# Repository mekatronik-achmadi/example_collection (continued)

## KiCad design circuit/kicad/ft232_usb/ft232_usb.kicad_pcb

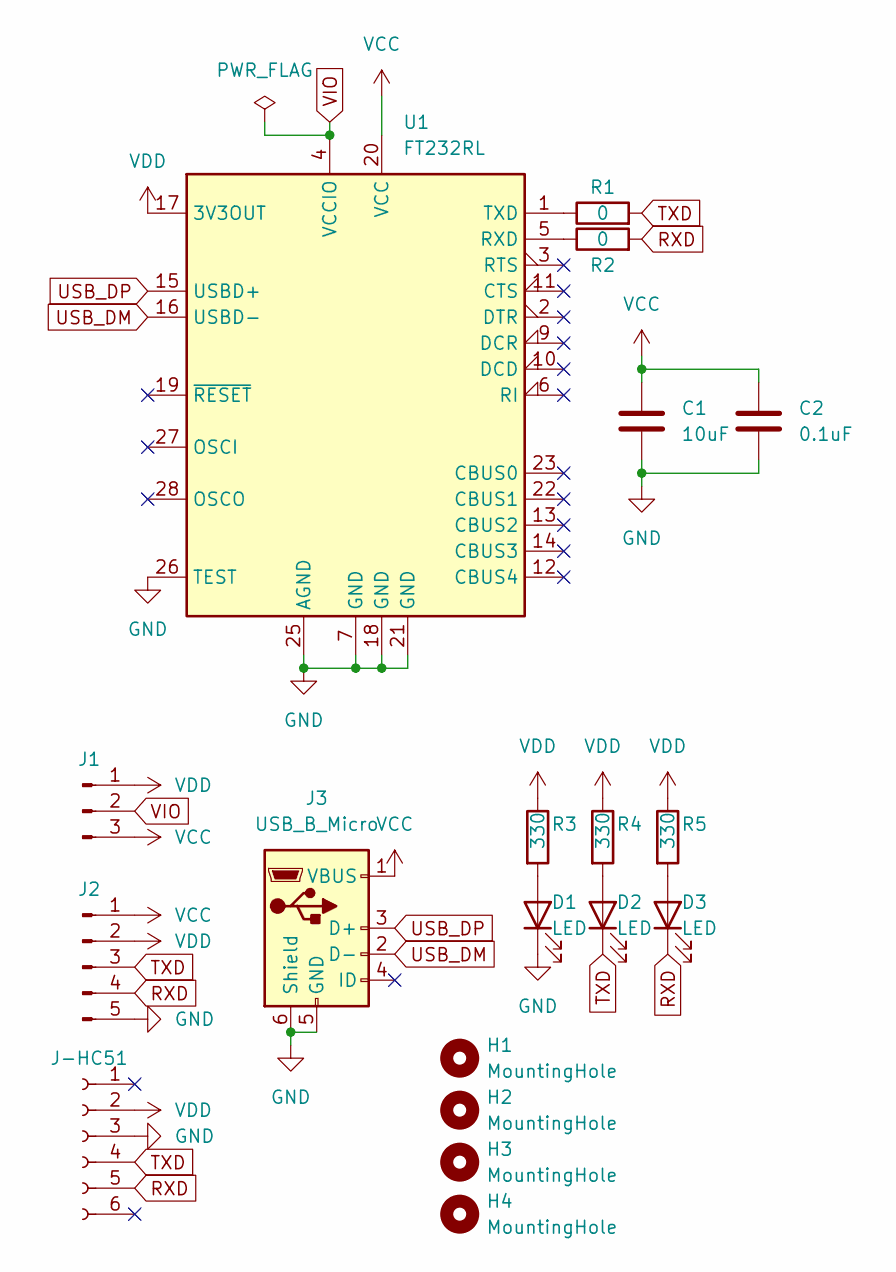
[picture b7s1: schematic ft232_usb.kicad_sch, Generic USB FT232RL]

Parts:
C1: 10uF; C_0805_2012Metric_Pad1.18x1.45mm_HandSolder
C2: 0.1uF; C_0805_2012Metric_Pad1.18x1.45mm_HandSolder
D1, D2, D3: LED; LED_0805_2012Metric_Pad1.15x1.40mm_HandSolder
H1, H2, H3, H4: MountingHole; MountingHole_2.2mm_M2_ISO7380_Pad
J1: Conn_01x03_Male; PinHeader_1x03_P2.54mm_Vertical
J2: Conn_01x05_Male; PinHeader_1x05_P2.54mm_Vertical
J3: USB_B_Micro; USB_Micro-B_Wuerth_629105150521
J-HC51: Conn_01x06_Female; PinSocket_1x06_P2.54mm_Vertical
R1, R2: 0; R_0805_2012Metric_Pad1.20x1.40mm_HandSolder
R3, R4, R5: 330; R_0805_2012Metric_Pad1.20x1.40mm_HandSolder
U1: FT232RL; SSOP-28_5.3x10.2mm_P0.65mm

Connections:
GND: C1.2, C2.2, D1.1 (K), J2.5, J3.5 (GND), J3.6 (Shield), J-HC51.3, U1.7 (GND), U1.18 (GND), U1.21 (GND), U1.25 (AGND), U1.26 (TEST)
unnamed: D1.2 (A), R3.2
unnamed: D2.2 (A), R4.2
unnamed: D3.2 (A), R5.2
unnamed: R1.1, U1.1 (TXD)
unnamed: R2.1, U1.5 (RXD)
RXD: D3.1 (K), J2.4, J-HC51.5, R2.2
TXD: D2.1 (K), J2.3, J-HC51.4, R1.2
USB_DM: J3.2 (D-), U1.16 (USBD-)
USB_DP: J3.3 (D+), U1.15 (USBD+)
VCC: C1.1, C2.1, J1.3, J2.1, J3.1 (VBUS), U1.20 (VCC)
VDD: J1.1, J2.2, J-HC51.2, R3.1, R4.1, R5.1, U1.17 (3V3OUT)
VIO: J1.2, U1.4 (VCCIO)

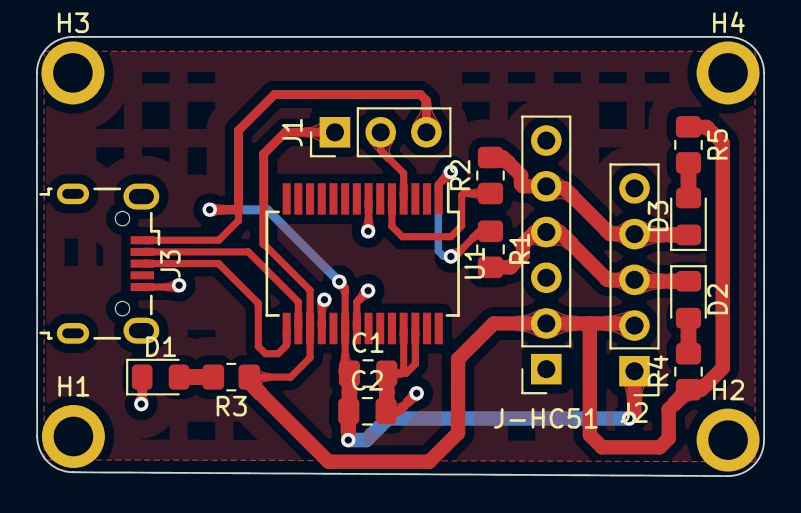
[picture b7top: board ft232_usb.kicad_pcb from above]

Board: 2 copper layers, 40.4 x 24.4 mm, 19 parts (0 on the bottom side), 13 nets.

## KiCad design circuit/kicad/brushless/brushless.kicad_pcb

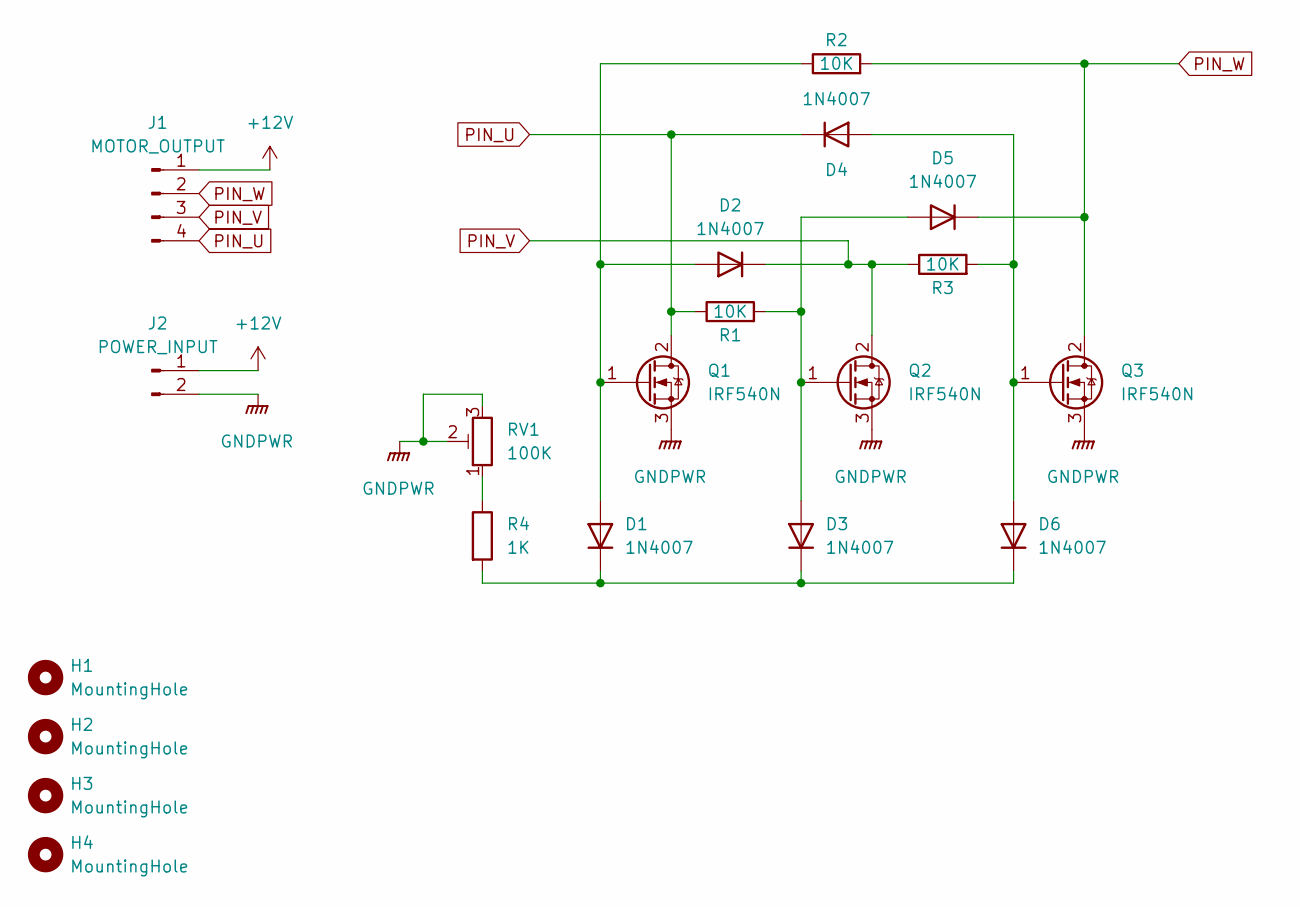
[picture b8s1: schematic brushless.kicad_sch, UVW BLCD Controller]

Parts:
D1, D2, D3, D4, D5, D6: 1N4007; D_SMA-SMB_Universal_Handsoldering
H1, H2, H3, H4: MountingHole; MountingHole_2.5mm
J1: MOTOR_OUTPUT; Altech_AK300_1x04_P5.00mm_45-Degree
J2: POWER_INPUT; Altech_AK300_1x02_P5.00mm_45-Degree
Q1, Q2, Q3: IRF540N; TO-263-2
R1, R2, R3: 10K; R_1206_3216Metric_Pad1.30x1.75mm_HandSolder
R4: 1K; R_1206_3216Metric_Pad1.30x1.75mm_HandSolder
RV1: 100K; Potentiometer_Bourns_3266W_Vertical

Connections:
+12V: J1.1, J2.1
GNDPWR: J2.2, Q1.3 (S), Q2.3 (S), Q3.3 (S), RV1.2, RV1.3
unnamed: D1.2 (A), D2.2 (A), Q1.1 (G), R2.1
unnamed: D3.2 (A), D5.2 (A), Q2.1 (G), R1.2
unnamed: D4.2 (A), D6.2 (A), Q3.1 (G), R3.2
unnamed: D1.1 (K), D3.1 (K), D6.1 (K), R4.2
unnamed: R4.1, RV1.1
PIN_U: D4.1 (K), J1.4, Q1.2 (D), R1.1
PIN_V: D2.1 (K), J1.3, Q2.2 (D), R3.1
PIN_W: D5.1 (K), J1.2, Q3.2 (D), R2.2

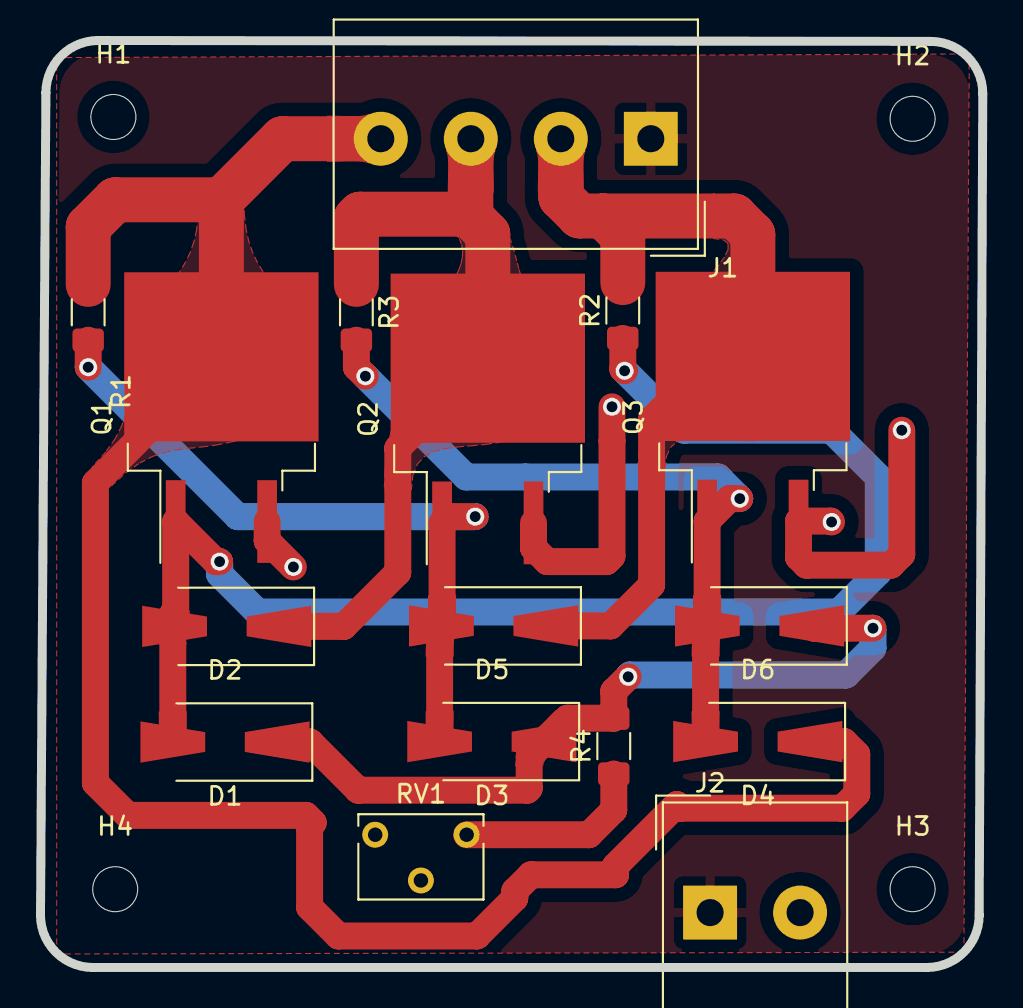
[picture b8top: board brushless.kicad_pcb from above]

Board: 2 copper layers, 52.3 x 51.5 mm, 20 parts (0 on the bottom side), 10 nets.

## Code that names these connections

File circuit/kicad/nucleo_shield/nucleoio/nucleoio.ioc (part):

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Mcu.Name=STM32F401R(D-E)Tx
Mcu.Package=LQFP64
Mcu.UserName=STM32F401RETx
PA10.Mode=Asynchronous
PA10.Signal=USART1_RX
PA13.GPIOParameters=GPIO_Label
PA13.GPIO_Label=TMS
PA13.Mode=Serial_Wire
PA13.Signal=SYS_JTMS-SWDIO
PA14.GPIOParameters=GPIO_Label
PA14.GPIO_Label=TCK
PA14.Mode=Serial_Wire
PA14.Signal=SYS_JTCK-SWCLK
PA15.Mode=NSS_Signal_Hard_Output
PA15.Signal=SPI3_NSS
PA2.GPIOParameters=GPIO_Speed,GPIO_PuPd,GPIO_Label,GPIO_Mode
PA2.GPIO_Label=USART_TX
PA2.GPIO_Mode=GPIO_MODE_AF_PP
PA2.GPIO_PuPd=GPIO_NOPULL
PA2.GPIO_Speed=GPIO_SPEED_FREQ_LOW
PA2.Mode=Asynchronous
PA2.Signal=USART2_TX
PA3.GPIOParameters=GPIO_Speed,GPIO_PuPd,GPIO_Label,GPIO_Mode
PA3.GPIO_Label=USART_RX
PA3.GPIO_Mode=GPIO_MODE_AF_PP
PA3.GPIO_PuPd=GPIO_NOPULL
PA3.GPIO_Speed=GPIO_SPEED_FREQ_LOW
PA3.Mode=Asynchronous
PA3.Signal=USART2_RX
PA5.GPIOParameters=GPIO_Speed,GPIO_PuPd,GPIO_Label,GPIO_Mode
PA5.GPIO_Label=LD2 [Green Led]
PA5.GPIO_Mode=GPIO_MODE_OUTPUT_PP
PA5.GPIO_PuPd=GPIO_NOPULL
PA5.GPIO_Speed=GPIO_SPEED_FREQ_LOW
PA5.Signal=GPIO_Output
PA9.Mode=Asynchronous
PA9.Signal=USART1_TX
PB2.Signal=GPIO_Input
PB3.GPIOParameters=GPIO_Label
PB3.GPIO_Label=SWO
PB3.Signal=SYS_JTDO-SWO
PC10.Mode=Full_Duplex_Master
PC10.Signal=SPI3_SCK
PC11.Mode=Full_Duplex_Master
PC11.Signal=SPI3_MISO
PC12.Mode=Full_Duplex_Master
PC12.Signal=SPI3_MOSI
PC13-ANTI_TAMP.GPIOParameters=GPIO_PuPd,GPIO_Label,GPIO_ModeDefaultEXTI
PC13-ANTI_TAMP.GPIO_Label=B1 [Blue PushButton]
PC13-ANTI_TAMP.GPIO_ModeDefaultEXTI=GPIO_MODE_IT_FALLING
PC13-ANTI_TAMP.GPIO_PuPd=GPIO_NOPULL
PC13-ANTI_TAMP.Signal=GPXTI13
PC14-OSC32_IN.Mode=LSE-External-Oscillator
PC14-OSC32_IN.Signal=RCC_OSC32_IN
PC15-OSC32_OUT.Mode=LSE-External-Oscillator
PC15-OSC32_OUT.Signal=RCC_OSC32_OUT
PH0\ -\ OSC_IN.Mode=HSE-External-Clock-Source
PH0\ -\ OSC_IN.Signal=RCC_OSC_IN
PH1\ -\ OSC_OUT.Mode=HSE-External-Clock-Source
PH1\ -\ OSC_OUT.Signal=RCC_OSC_OUT
RCC.HSE_VALUE=8000000
RCC.SYSCLKFreq_VALUE=84000000
RCC.SYSCLKSource=RCC_SYSCLKSOURCE_PLLCLK
board=NUCLEO-F401RE
boardIOC=true

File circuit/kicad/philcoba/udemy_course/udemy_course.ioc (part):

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Mcu.Name=STM32F103C(8-B)Tx
Mcu.Package=LQFP48
Mcu.UserName=STM32F103C8Tx
PA11.Mode=Device
PA11.Signal=USB_DM
PA12.Mode=Device
PA12.Signal=USB_DP
PA13.Mode=Serial_Wire
PA13.Signal=SYS_JTMS-SWDIO
PA14.Mode=Serial_Wire
PA14.Signal=SYS_JTCK-SWCLK
PB10.Mode=I2C
PB10.Signal=I2C2_SCL
PB11.Mode=I2C
PB11.Signal=I2C2_SDA
PB6.Mode=Asynchronous
PB6.Signal=USART1_TX
PB7.Mode=Asynchronous
PB7.Signal=USART1_RX
PC13-TAMPER-RTC.Signal=GPIO_Output
PD0-OSC_IN.Mode=HSE-External-Oscillator
PD0-OSC_IN.Signal=RCC_OSC_IN
PD1-OSC_OUT.Mode=HSE-External-Oscillator
PD1-OSC_OUT.Signal=RCC_OSC_OUT
RCC.SYSCLKFreq_VALUE=48000000
RCC.SYSCLKSource=RCC_SYSCLKSOURCE_PLLCLK
board=custom

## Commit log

2021-11-26 first Flutter
2021-11-26 first atmega
2021-11-26 more atmega
2021-11-26 first esp8266
2021-11-26 mqtt esp8266
2021-11-26 doorwatch esp8266
2021-11-26 phtdsmeter esp8266
2021-11-26 first rtos esp8266
2021-11-26 esp8266
2021-11-27 first stm32
2021-11-27 stm32
2021-11-27 m2560_las_orbit
2021-11-29 ta nya didin
2021-11-30 stm32 more examples
2021-12-15 f429disc examples
2021-12-15 c webkit
2021-12-15 new circuit
2021-12-15 mega16_training
2021-12-15 wxserial
2021-12-16 more kicad examples
2021-12-16 gtk examples
2021-12-16 java examples
2021-12-16 octave examples
2021-12-16 more examples
2021-12-16 python academic examples
2021-12-16 qt examples
2021-12-16 stm32 chibios examples
2021-12-16 finish selecting examples
2021-12-16 clean-up unnecessary non text files
2021-12-16 some stm32 examples
2021-12-16 esp32 examples
2022-01-05 update stm32 sensor example
2022-01-11 Mini PV
2022-01-11 PCB Mini PV
2022-01-16 esp32 blink
2022-01-16 esp8266 example
2022-02-18 papank PCB
2022-02-18 esp32 dsp example
2022-02-18 ESP DSP FFT is weird
2022-02-19 esp32 mic fft doxygen
2022-02-19 esp32 mic fft doxygen dark
2022-02-20 doxygen
2022-02-25 KiCAD tutorial
2022-02-26 SMD Tutorial
2022-03-04 wxWidget CPP
2022-03-14 btserial
2022-03-14 btserial_keypad
2022-03-14 btspp
2022-03-14 btspp OLED
2022-03-14 btspp string handle
2022-03-14 bt spp text handler
2022-03-15 string/char handler error
2022-03-15 need handle sring more than 20
2022-03-15 string handle
2022-03-15 40 strings OK
2022-03-15 first demo
2022-03-15 Include PDF schematic
2022-03-24 coba js server
2022-04-09 stm32 driver
2022-05-21 pid example in python
2022-07-20 ESP32 IDF Arduino Example
2022-07-20 ESP OLED IDF
2022-07-20 ESP IDF
2022-07-20 ESP32 OLED IDF
2022-07-20 ESP32 IDF OLED
2022-07-20 ESP32 OLED Arduino
2022-07-20 ESP32 Arduino
2022-07-20 Typo
2022-07-20 Arduino sucks
2022-07-21 ESP32 Arduino compileable but LCD blank
2022-07-21 ESP32 Arduino OLED Example
2022-07-21 ESP32 Arduino OLED done
2022-09-08 ESP32 Audio Tester
2022-09-08 Schematic Done
2022-09-08 ESP32 Audio
2022-09-20 some examples
2022-10-02 ESP32 AP Webserver
2022-10-02 ESP32 Version
2022-10-02 ESP32 HTTPD
2022-12-27 KiCAD JLC Tutorial
2022-12-27 KiCAD JLC
2022-12-31 Serial Example
2022-12-31 WX serial
2022-12-31 Cross Serial Terminal wxWidget
2022-12-31 Cross Serial Terminal Qt
2022-12-31 Cross Serial Qt
2023-01-01 Cross Serial Gtk
2023-01-02 GTK is so weird
2023-01-02 GTK GUI Serial
2023-01-02 GTK is weird
2023-01-02 Readme Cross Serial
2023-01-03 Gtk has no input dialog like Qt or wxWidgets
2023-01-03 Port/Baudrate no Input Dialog
2023-01-03 Cross Serial Qt Update
2023-01-03 Some basic AVR example
2023-01-03 AVR Basic Example
2023-01-03 Basic AVR example
2023-01-06 CodeVisionAVR on Simulide
2023-01-15 OptoIsolate Example
2023-01-16 UVW BLDC Example
2023-01-16 Learn JLCPCB
2023-01-26 Migrate Eagle-KiCAD: FT232RL
2023-01-26 Migrate Eagle-KiCAD: USBASP
2023-01-26 Migrate Eagle-KiCAD
2023-03-23 Some Academic Python Tools
2023-03-23 Some Academic Python tool
2023-03-23 Some Academic Tool
2023-03-23 Some Academic Tools First Run OK
2023-03-23 Some Academic Python Tool OK
2023-03-24 STM32 board
2023-03-25 STM32PP
2023-03-25 STM32 PP
2023-04-14 STM32 UART Example
2023-05-10 JSON C
2023-05-11 C JSON Collections
2023-05-11 JSON C Library
2023-05-11 JSON C example
2023-05-13 Tes JSON
2023-05-15 Parse String without strtok
2023-05-15 Parse Text
2023-06-07 STM32 KiCAD Example from Phils-Lab
2023-06-25 Shield Nucleo
2023-06-25 Nucleo Shield
2023-07-09 Recursive Example
2023-07-09 Try on ESP8266
2023-07-09 SinC on ESP8266
2023-08-17 STM32 LQFP64 Minimum System
2023-08-17 Progress
2023-08-17 Coba Pesan
2023-08-17 Ordering
2023-08-18 Update PCB to be Smaller
2023-08-18 update PCB
2023-08-27 Update PCB LQFP64
2023-08-27 Gerber LQFP64
2023-08-27 Uodate LQFP64
2023-09-11 Gtkmm examples
2023-10-09 ESP12-F Module
2023-10-09 ESP12-F
2023-10-09 ESP12F
2023-10-09 ESP-12F
2023-10-09 Kuliah Sinyal Ngulang
2023-10-30 Trying LoRA
2023-10-30 Lora Sender Arduino
2023-10-30 LoRA Arduino Receiver
2023-10-30 Arduino LoRA OK
2023-11-06 STM32 Arduino LoRA
2023-11-06 LoRA STM32 seem disconnected
2023-11-06 STM32 Arduino LoRA not work
2023-11-06 LoRA Chibios Porting
2023-11-06 CHibiOS Lora
2023-11-07 Arduino STM32 LoRA
2023-11-07 STM32 BluePill Lora Failed
2023-11-07 LoRa STM32 to AVR OK
2023-11-07 Lora AVR to STM32 OK
2023-11-07 LoRA Sender only
2023-11-07 Incomplete Sending Data
2023-11-07 Its working as byte data
2023-11-07 Send data in bytes
2023-11-07 Start Working on STM32 LoRA receiver
2023-11-07 Start Working on Receiver
2023-11-07 LoRa CHibiOS
2023-11-07 LoRA receiver STM32
2023-11-09 LoRa STM32 Improvements
2023-11-09 LoRA example OK
2023-11-09 Number Sending
2023-11-09 LoRA Plot
2023-12-11 STM8 Blink
2023-12-11 STM8 Examples
2023-12-11 STM8 is simpler but harder
2023-12-18 wxWidget Serial Terminal
2024-01-15 Gtk Vala
2024-02-16 ESP32 Mic
2024-02-16 ESP32 Sound In
2024-02-16 ESP Sound
2024-02-17 Mic Failed
2024-02-17 SPH0645 All Zero
2024-02-17 SPH0645 No Work
2024-02-17 Plot Mic
2024-02-18 Sound Input esp8266
2024-02-18 ESP Sound In
2024-02-18 ESP8266 Mic
2024-02-18 SPH0645 Still Zero
2024-02-18 SPH0645 Pio not work
2024-02-19 Drop ESP8288 as too slow for I2S Mic
2024-02-19 Retry ESP8266 I2S Mic
2024-02-19 ESP8266 I2S Mic Not Work
2024-02-20 Rewiring
2024-02-20 I2S Mic all Zero
2024-02-20 Still Zero
2024-02-20 Its not zero but weird
2024-02-20 Move ESP32 Mic to PlatformIO
2024-02-20 ESP32 I2S work on IDF so far
2024-02-21 PlatformIO ESP32 Mic
2024-02-21 Mic ESP32
2024-02-21 ESP32 PIO
2024-02-21 PIO VSCode
2024-02-23 Serial Plot
2024-02-23 Python Serial Plot
2024-02-24 PlatformIO Notes
2024-02-26 PlatformIO Menu
2024-02-28 Use VSCode C_CPP
2024-02-29 PIO verbose
2024-03-02 VSCode Intellisense
2024-03-07 Notes
2024-03-09 Rust Example
2024-03-10 Rust Examples
2024-03-12 Rust Array
2024-03-13 Rust Thread
2024-03-14 Rust Note
2024-03-18 Qt Serial Terminal
2024-03-18 Old Serial Qt5
2024-03-19 FLTK Serial Failed
2024-03-19 FLTK Examples
2024-03-22 Some Updates
2024-03-22 GoLang example
2024-03-25 RustFMT examples
2024-03-27 C Pointer
2024-03-31 Drop FLTK Examples
2024-04-04 NodeJS example
2024-04-04 NodeJS HTML Half Failed
